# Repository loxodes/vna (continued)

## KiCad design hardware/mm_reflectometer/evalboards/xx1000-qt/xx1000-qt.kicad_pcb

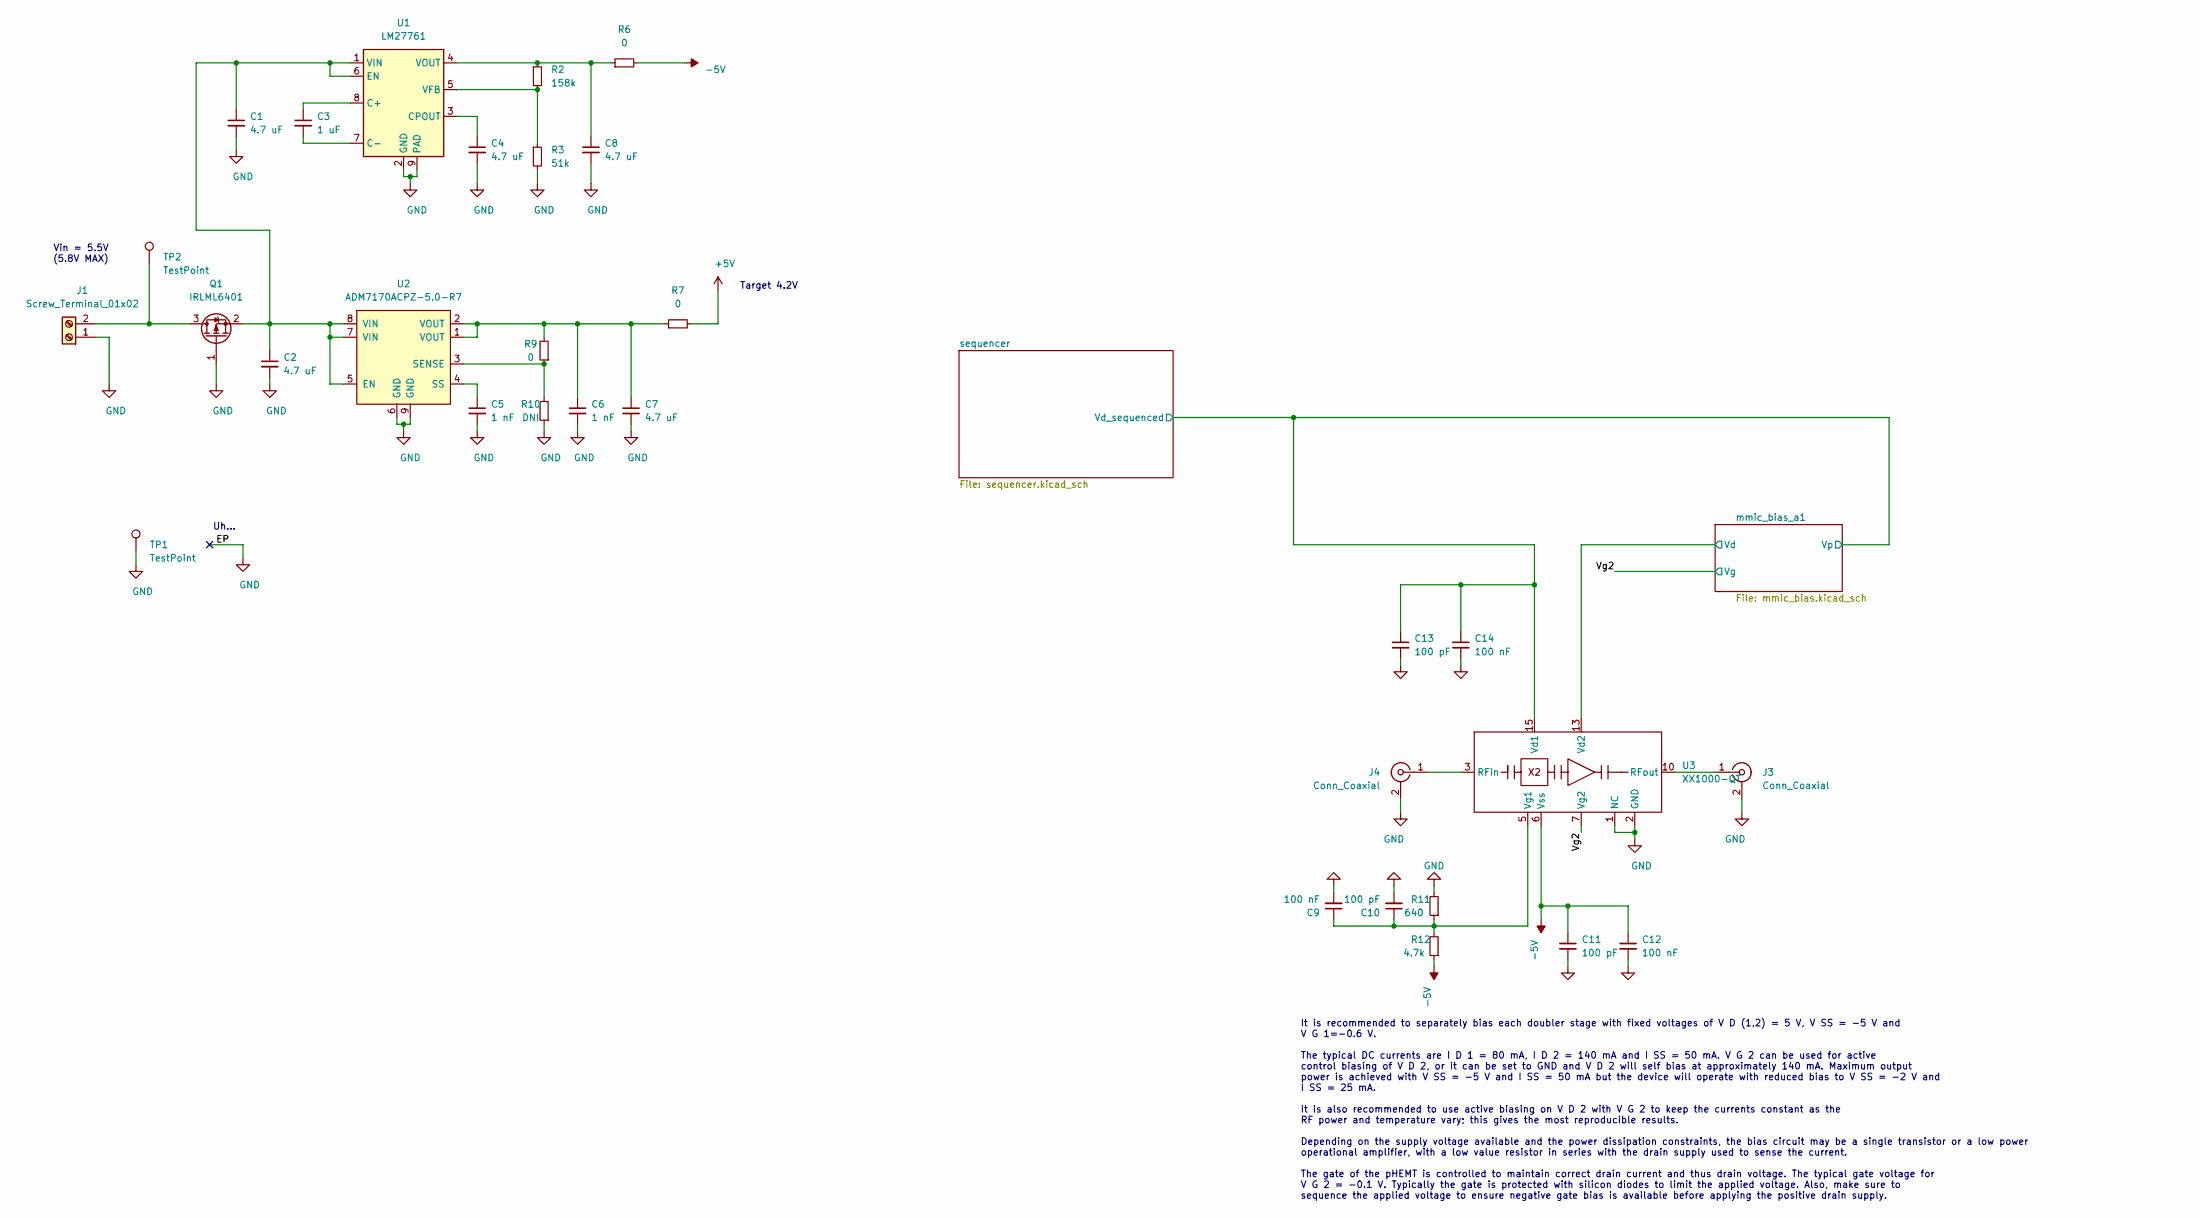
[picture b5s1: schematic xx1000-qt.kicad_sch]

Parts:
C1, C2, C4, C7, C8: 4.7 uF; C_0603_1608Metric
C3: 1 uF; C_0402_1005Metric
C5, C6: 1 nF; C_0402_1005Metric
C9, C12, C14: 100 nF; C_0402_1005Metric
C10, C11, C13: 100 pF; C_0402_1005Metric
J1: Screw_Terminal_01x02; TerminalBlock_Phoenix_MPT-0,5-2-2.54_1x02_P2.54mm_Horizontal
J3, J4: Conn_Coaxial; sw_edge_oshpark_4layer
Q1: IRLML6401; SOT-23
R2: 158k; R_0402_1005Metric
R3: 51k; R_0402_1005Metric
R6, R7, R9: 0; R_0402_1005Metric
R10: DNI; R_0402_1005Metric
R11: 640; R_0402_1005Metric
R12: 4.7k; R_0402_1005Metric
TP1, TP2: TestPoint; TestPoint_Keystone_5015_Micro-Minature
U1: LM27761; WSON-8-1EP_2x2mm_P0.5mm_EP0.9x1.6mm
U2: ADM7170ACPZ-5.0-R7; DFN-8-1EP_3x3mm_P0.5mm_EP1.66x2.38mm
U3: XX1000-QT; QFN-16-1EP_3x3mm_P0.5mm_EP1.45x1.45mm; mpn XX1000-QT-0G0T

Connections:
+5V: R7.2; also elsewhere on the board
-5V: C11.1, C12.1, R6.2, R12.1, U3.6 (Vss); also elsewhere on the board
/Vg2: U3.7 (Vg2); also elsewhere on the board
/mmic_bias_a1/Vd: U3.13 (Vd2); also elsewhere on the board
/mmic_bias_a1/Vp: C13.1, C14.1, U3.15 (Vd1); also elsewhere on the board
GND: C1.2, C2.2, C4.2, C5.2, C6.2, C7.2, C8.2, C9.2, C10.2, C11.2, C12.2, C13.2, C14.2, J1.1, J3.2 (Ext), J4.2 (Ext), Q1.1 (G), R3.2, R10.1, R11.2, TP1.1, U1.2 (GND), U1.9 (PAD), U2.6 (GND), U2.9 (GND), U3.1 (NC), U3.2 (GND), U3.4 (GND), U3.8 (NC), U3.9 (GND), U3.11 (GND), U3.12 (NC), U3.14 (NC), U3.16 (NC), U3.17 (GND); also elsewhere on the board
unnamed: C1.1, C2.1, Q1.2 (S), U1.1 (VIN), U1.6 (EN), U2.5 (EN), U2.7 (VIN), U2.8 (VIN)
unnamed: C3.1, U1.8 (C+)
unnamed: C3.2, U1.7 (C-)
unnamed: C4.1, U1.3 (CPOUT)
unnamed: C5.1, U2.4 (SS)
unnamed: C6.1, C7.1, R7.1, R9.2, U2.1 (VOUT), U2.2 (VOUT)
unnamed: C8.1, R2.1, R6.1, U1.4 (VOUT)
unnamed: C9.1, C10.1, R11.1, R12.2, U3.5 (Vg1)
unnamed: J1.2, Q1.3 (D), TP2.1
unnamed: J3.1 (In), U3.10 (RFout)
unnamed: J4.1 (In), U3.3 (RFin)
unnamed: R2.2, R3.1, U1.5 (VFB)
unnamed: R9.1, R10.2, U2.3 (SENSE)

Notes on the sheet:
Vin = 5.5V (5.8V MAX)
Uh...
Target 4.2V
It is recommended to separately bias each doubler stage with fixed voltages of V D (1,2) = 5 V, V SS = -5 V and V G 1=-0.6 V. The typical DC currents are I D 1 = 80 mA, I D 2 = 140 mA and I SS = 50 mA. V G 2 can be used for active control biasing of V D 2, or it can be set to GND and V D 2 will sel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

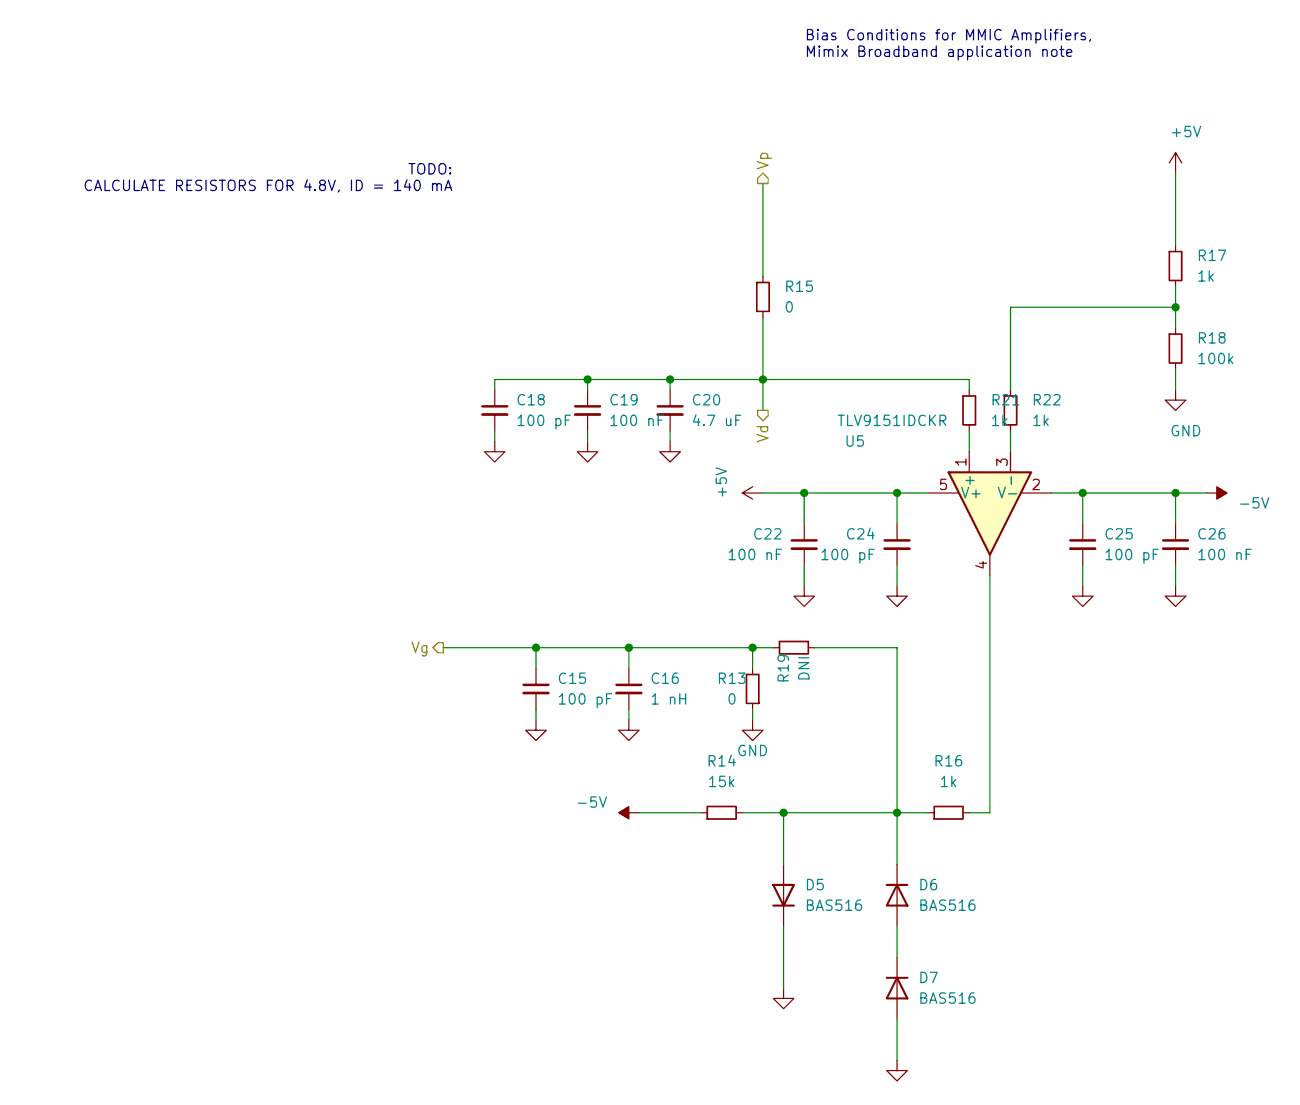
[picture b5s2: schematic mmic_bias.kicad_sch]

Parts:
C15, C18, C24, C25: 100 pF; C_0402_1005Metric
C16: 1 nH; C_0402_1005Metric
C19, C22, C26: 100 nF; C_0402_1005Metric
C20: 4.7 uF; C_0603_1608Metric
D5, D6, D7: BAS516; D_SOD-523
R13: 0; R_0402_1005Metric
R14: 15k; R_0402_1005Metric
R15: 0; R_0603_1608Metric
R16, R17, R21, R22: 1k; R_0402_1005Metric
R18: 100k; R_0402_1005Metric
R19: DNI; R_0402_1005Metric
U5: TLV9151IDCKR; SOT-353_SC-70-5

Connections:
+5V: C22.1, C24.1, R17.1, U5.5 (V+); also elsewhere on the board
-5V: C25.1, C26.1, R14.1, U5.2 (V-); also elsewhere on the board
/Vg2: C15.1, C16.1, R13.2, R19.2; also elsewhere on the board
/mmic_bias_a1/Vd: C18.1, C19.1, C20.1, R15.2, R21.1; also elsewhere on the board
/mmic_bias_a1/Vp: R15.1; also elsewhere on the board
GND: C15.2, C16.2, C18.2, C19.2, C20.2, C22.2, C24.2, C25.2, C26.2, D5.1 (K), D7.2 (A), R13.1, R18.2; also elsewhere on the board
unnamed: D5.2 (A), D6.1 (K), R14.2, R16.1, R19.1
unnamed: D6.2 (A), D7.1 (K)
unnamed: R16.2, U5.4
unnamed: R17.2, R18.1, R22.1
unnamed: R21.2, U5.1 (+)
unnamed: R22.2, U5.3 (-)

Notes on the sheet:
TODO: CALCULATE RESISTORS FOR 4.8V, ID = 140 mA
Bias Conditions for MMIC Amplifiers, Mimix Broadband application note

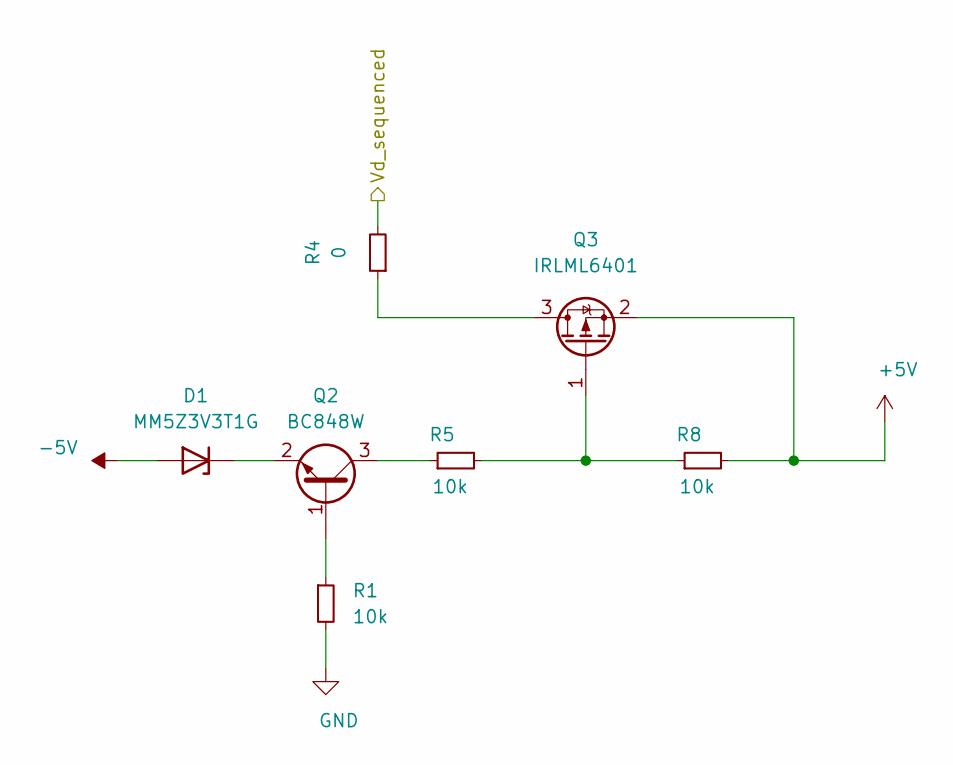
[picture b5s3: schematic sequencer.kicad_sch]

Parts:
D1: MM5Z3V3T1G; D_SOD-523
Q2: BC848W; SOT-323_SC-70
Q3: IRLML6401; SOT-23
R1, R5, R8: 10k; R_0402_1005Metric
R4: 0; R_0402_1005Metric

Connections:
+5V: Q3.2 (S), R8.2; also elsewhere on the board
-5V: D1.2 (A); also elsewhere on the board
/mmic_bias_a1/Vp: R4.2; also elsewhere on the board
GND: R1.2; also elsewhere on the board
unnamed: D1.1 (K), Q2.2 (E)
unnamed: Q2.1 (B), R1.1
unnamed: Q2.3 (C), R5.1
unnamed: Q3.1 (G), R5.2, R8.1
unnamed: Q3.3 (D), R4.1

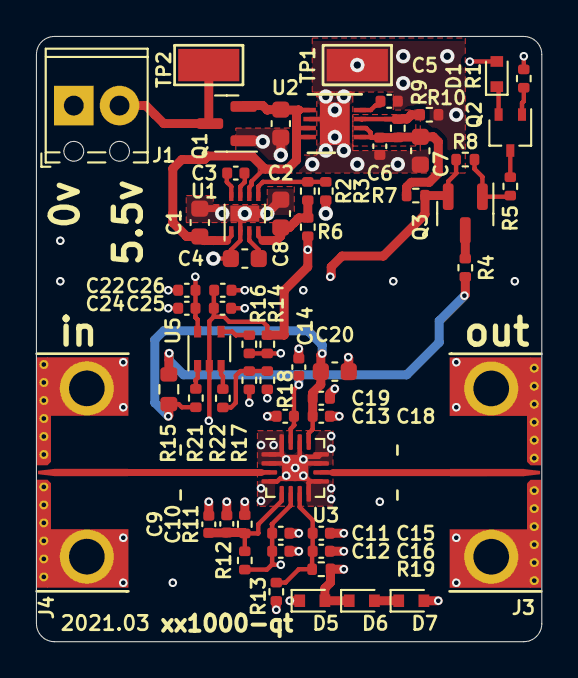
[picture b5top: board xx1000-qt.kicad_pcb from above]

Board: 4 copper layers, 28.1 x 33.6 mm, 60 parts (0 on the bottom side), 30 nets.

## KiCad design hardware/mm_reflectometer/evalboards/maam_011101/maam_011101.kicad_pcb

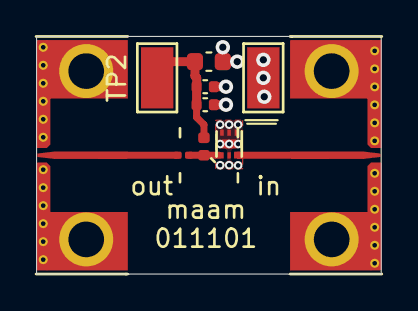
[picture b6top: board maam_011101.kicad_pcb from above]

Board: 4 copper layers, 19.2 x 13.2 mm, 10 parts (0 on the bottom side), 4 nets.

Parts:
C1: 100 pF; C_0402_1005Metric
C2: 100 pF; C_0201_0603Metric
C3: 100 nF; C_0402_1005Metric
C4: 10 uF; C_0603_1608Metric
J1, J2: Conn_Coaxial; sw_edge_oshpark_4layer
L1: BLM15GG471; L_0402_1005Metric
TP1, TP2: TestPoint; TestPoint_Keystone_5015_Micro-Minature
U1: MAAM-011101; TDFN6

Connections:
GND: C1.2, C3.2, C4.2, J1.2 (Ext), J2.2 (Ext), TP1.1, U1.2 (NC), U1.4 (NC), U1.5 (NC), U1.6 (NC), U1.7 (EP)
unnamed: C1.1, C3.1, C4.1, L1.1, TP2.1
unnamed: C2.1, L1.2, U1.1 (RFout)
unnamed: J2.1 (In), U1.3 (RFin)

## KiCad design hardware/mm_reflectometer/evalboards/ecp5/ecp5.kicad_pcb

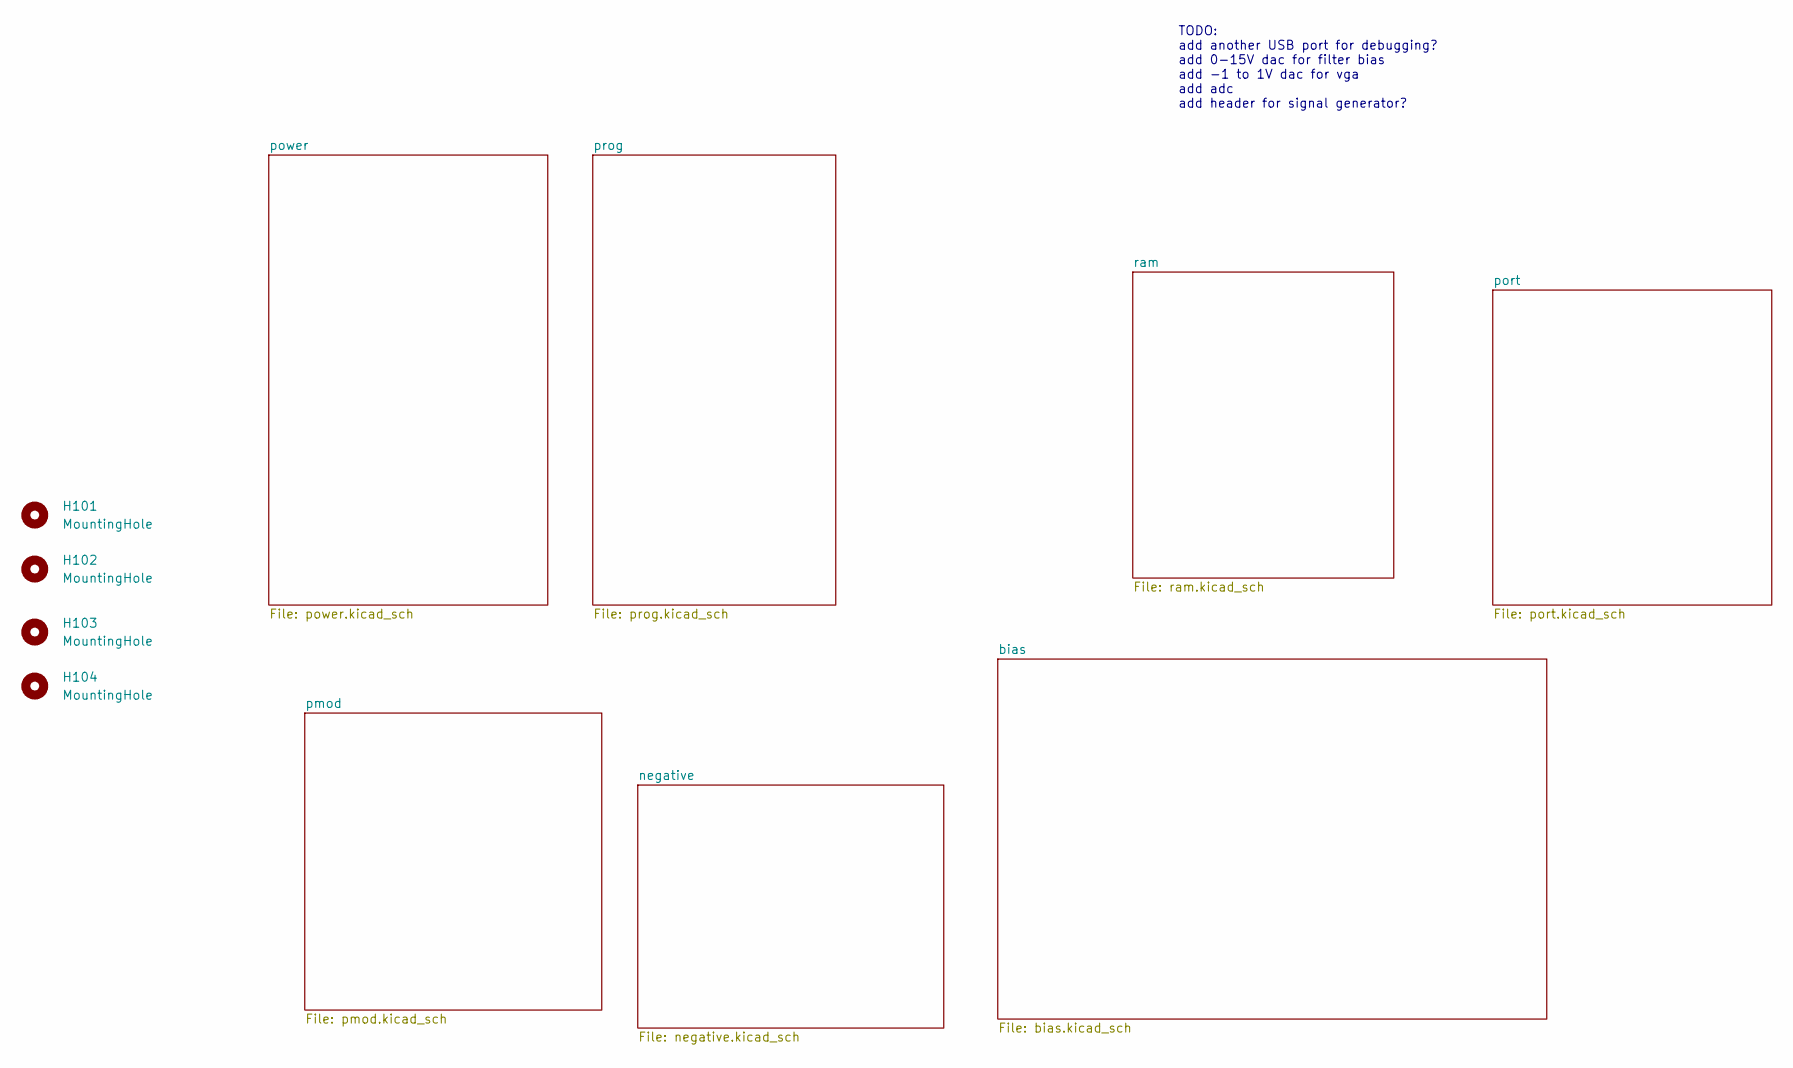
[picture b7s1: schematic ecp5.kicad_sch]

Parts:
H101, H102, H103, H104: MountingHole; MountingHole_2.7mm_M2.5

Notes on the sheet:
TODO: add another USB port for debugging? add 0-15V dac for filter bias add -1 to 1V dac for vga add adc add header for signal generator?

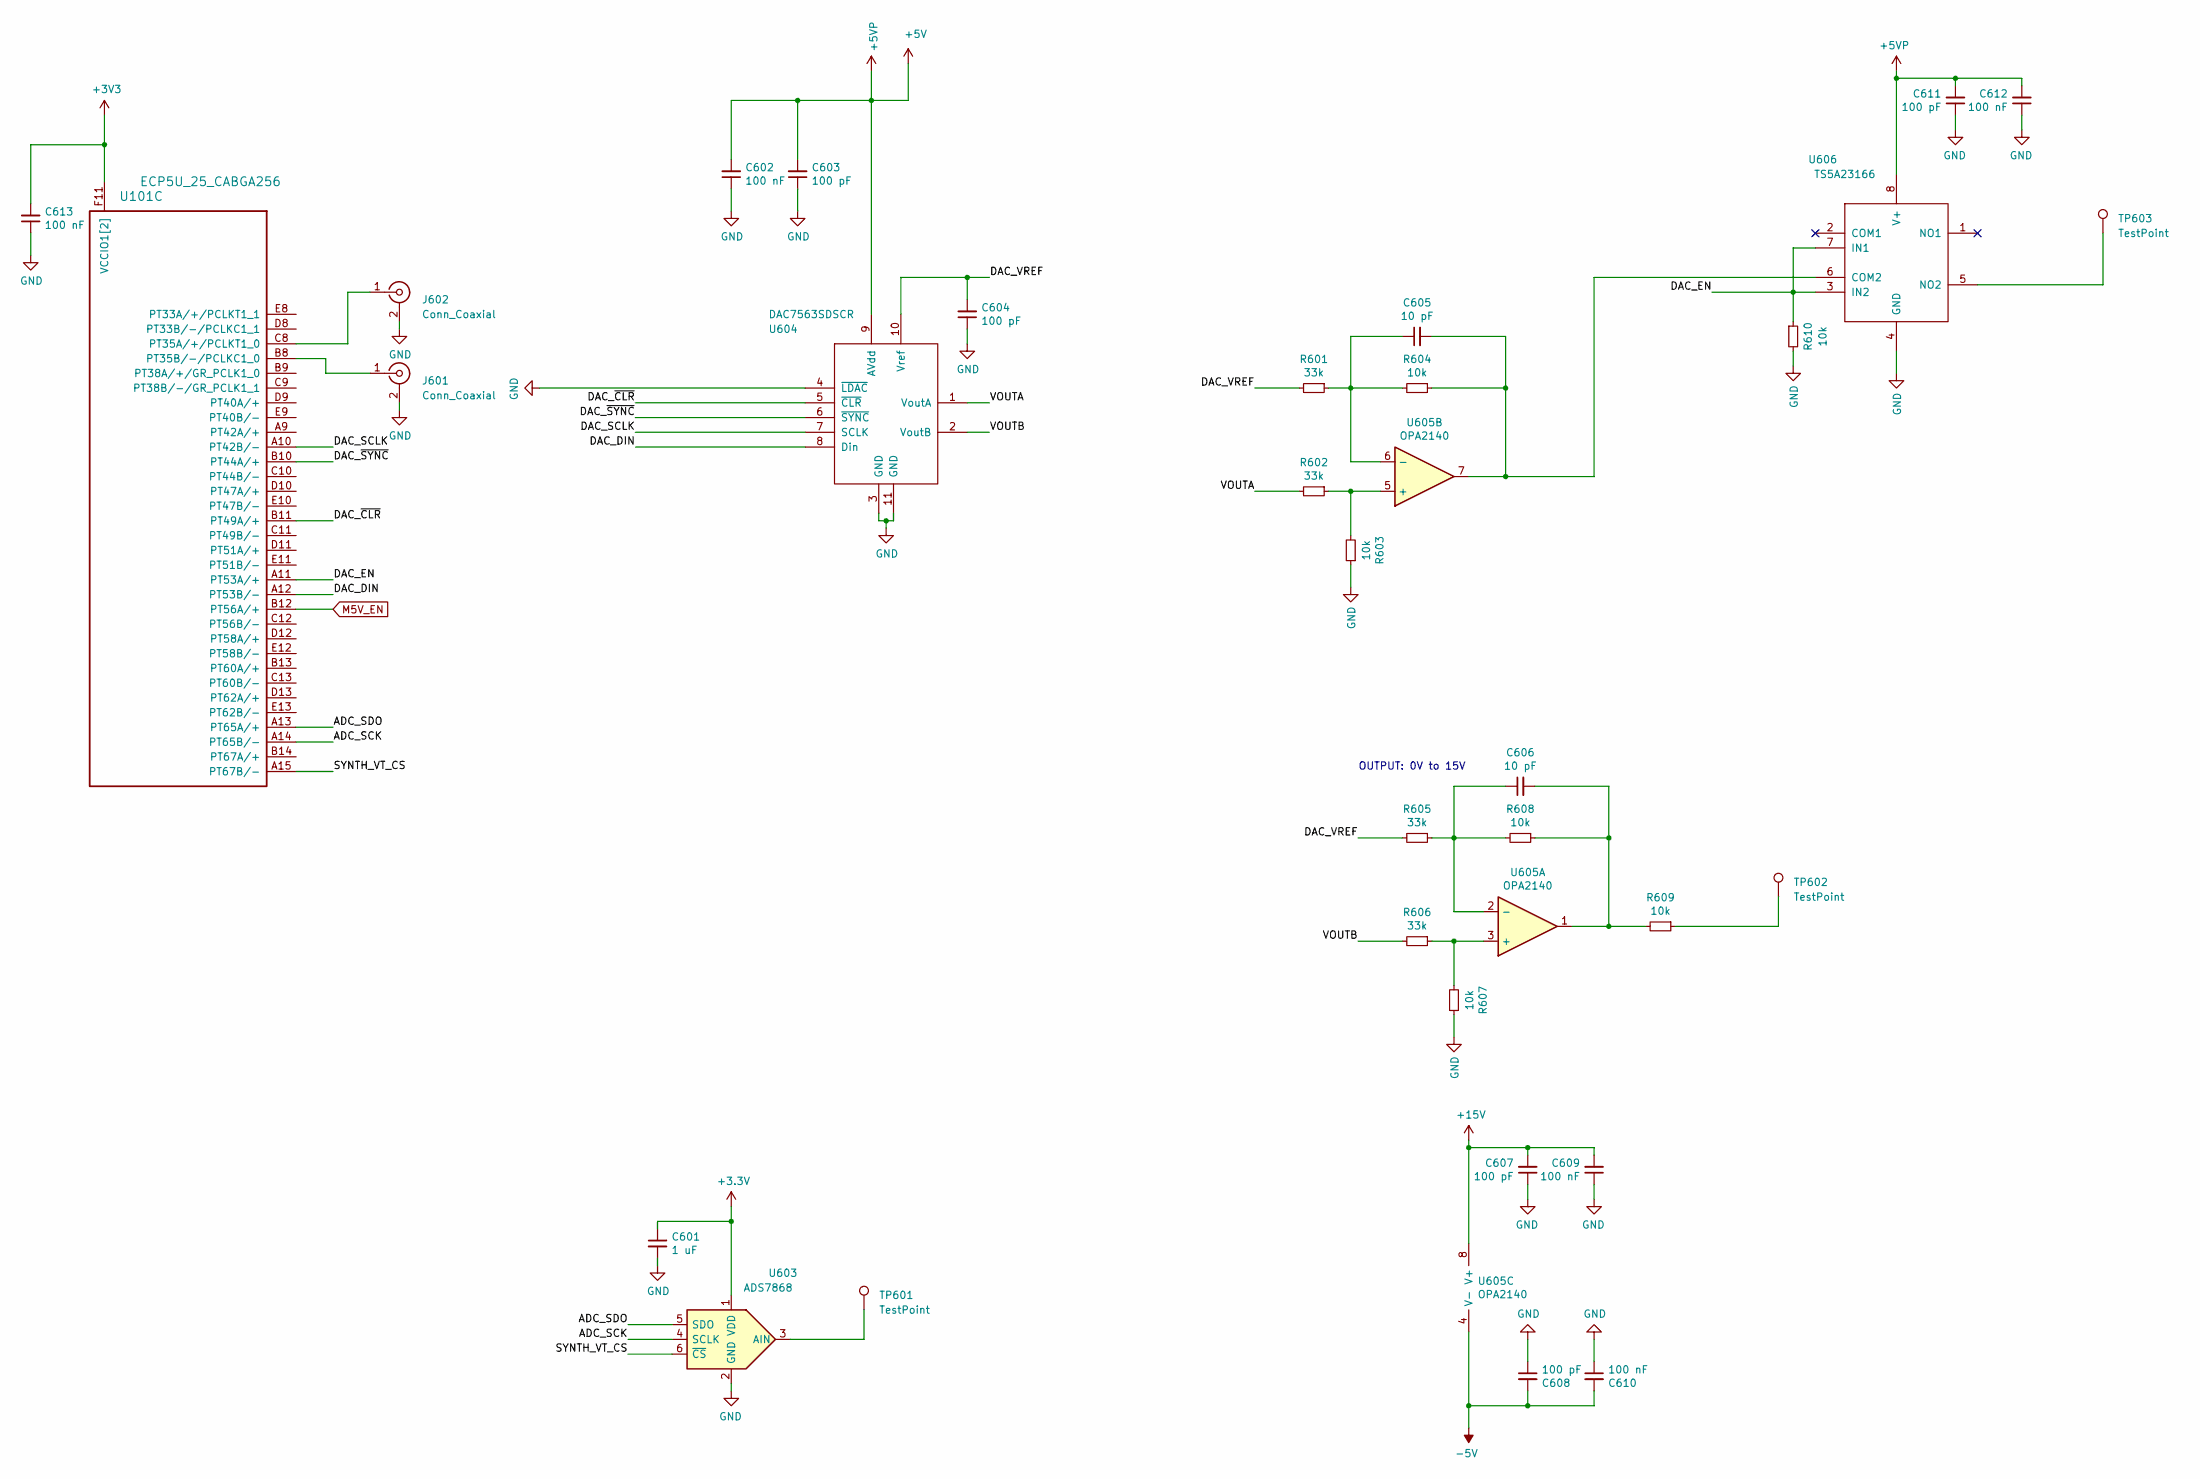
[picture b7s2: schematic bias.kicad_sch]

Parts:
C601: 1 uF; C_0402_1005Metric
C602, C609, C610, C612, C613: 100 nF; C_0402_1005Metric
C603, C604, C607, C608, C611: 100 pF; C_0402_1005Metric
C605, C606: 10 pF; C_0402_1005Metric
J601, J602: Conn_Coaxial; U.FL_Molex_MCRF_73412-0110_Vertical
R601, R602, R605, R606: 33k; R_0402_1005Metric
R603, R604, R607, R608, R609, R610: 10k; R_0402_1005Metric
TP601, TP602, TP603: TestPoint; TestPoint_Keystone_5015_Micro-Minature
U101: ECP5U_25_CABGA256; BGA-256_14.0x14.0mm_Layout16x16_P0.8mm_Ball0.45mm_Pad0.32mm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
U603: ADS7868; TSOT-23-6
U604: DAC7563SDSCR; DFN-10_PWSON_N10_3x3mm_P0.5mm_EP1.05x2.55mm
U605: OPA2140; MSOP-8_3x3mm_P0.65mm
U606: TS5A23166; VSSOP-8

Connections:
+5V: C602.2, C603.2, C611.2, C612.2, U604.9 (AVdd), U606.8 (V+); also elsewhere on the board
+15V: C607.2, C609.2, U605.8 (V+); also elsewhere on the board
-5V: C608.2, C610.2, U605.4 (V-); also elsewhere on the board
/bias/ADC_SCK: U101.A14 (PT65B/-), U603.4 (SCLK)
/bias/ADC_SDO: U101.A13 (PT65A/+), U603.5 (SDO)
/bias/DAC_DIN: U101.A12 (PT53B/-), U604.8 (Din)
/bias/DAC_EN: R610.1, U101.A11 (PT53A/+), U606.3 (IN2), U606.7 (IN1)
/bias/DAC_SCLK: U101.A10 (PT42B/-), U604.7 (SCLK)
/bias/DAC_VREF: C604.2, R601.2, R605.2, U604.10 (Vref)
/bias/DAC_~CLR: U101.B11 (PT49A/+), U604.5 (~CLR)
/bias/DAC_~SYNC: U101.B10 (PT44A/+), U604.6 (~SYNC)
/bias/SYNTH_VT_CS: U101.A15 (PT67B/-), U603.6 (~CS)
/bias/VOUTA: R602.2, U604.1 (VoutA)
/bias/VOUTB: R606.2, U604.2 (VoutB)
GND: C601.2, C602.1, C603.1, C604.1, C607.1, C608.1, C609.1, C610.1, C611.1, C612.1, C613.1, J601.2 (Ext), J602.2 (Ext), R603.1, R607.1, R610.2, U603.2 (GND), U604.3 (GND), U604.4 (~LDAC), U604.11 (GND), U606.4 (GND); also elsewhere on the board
M5V_EN: U101.B12 (PT56A/+); also elsewhere on the board
unnamed: C605.1, R601.1, R604.2, U605.6 (-)
unnamed: C605.2, R604.1, U605.7, U606.6 (COM2)
unnamed: C606.1, R605.1, R608.2, U605.2 (-)
unnamed: C606.2, R608.1, R609.2, U605.1
unnamed: J601.1 (In), U101.B8 (PT35B/-/PCLKC1_0)
unnamed: J602.1 (In), U101.C8 (PT35A/+/PCLKT1_0)
unnamed: R602.1, R603.2, U605.5 (+)
unnamed: R606.1, R607.2, U605.3 (+)
unnamed: R609.1, TP602.1
unnamed: TP601.1, U603.3 (AIN)
unnamed: TP603.1, U606.5 (NO2)

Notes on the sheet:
OUTPUT: 0V to 15V

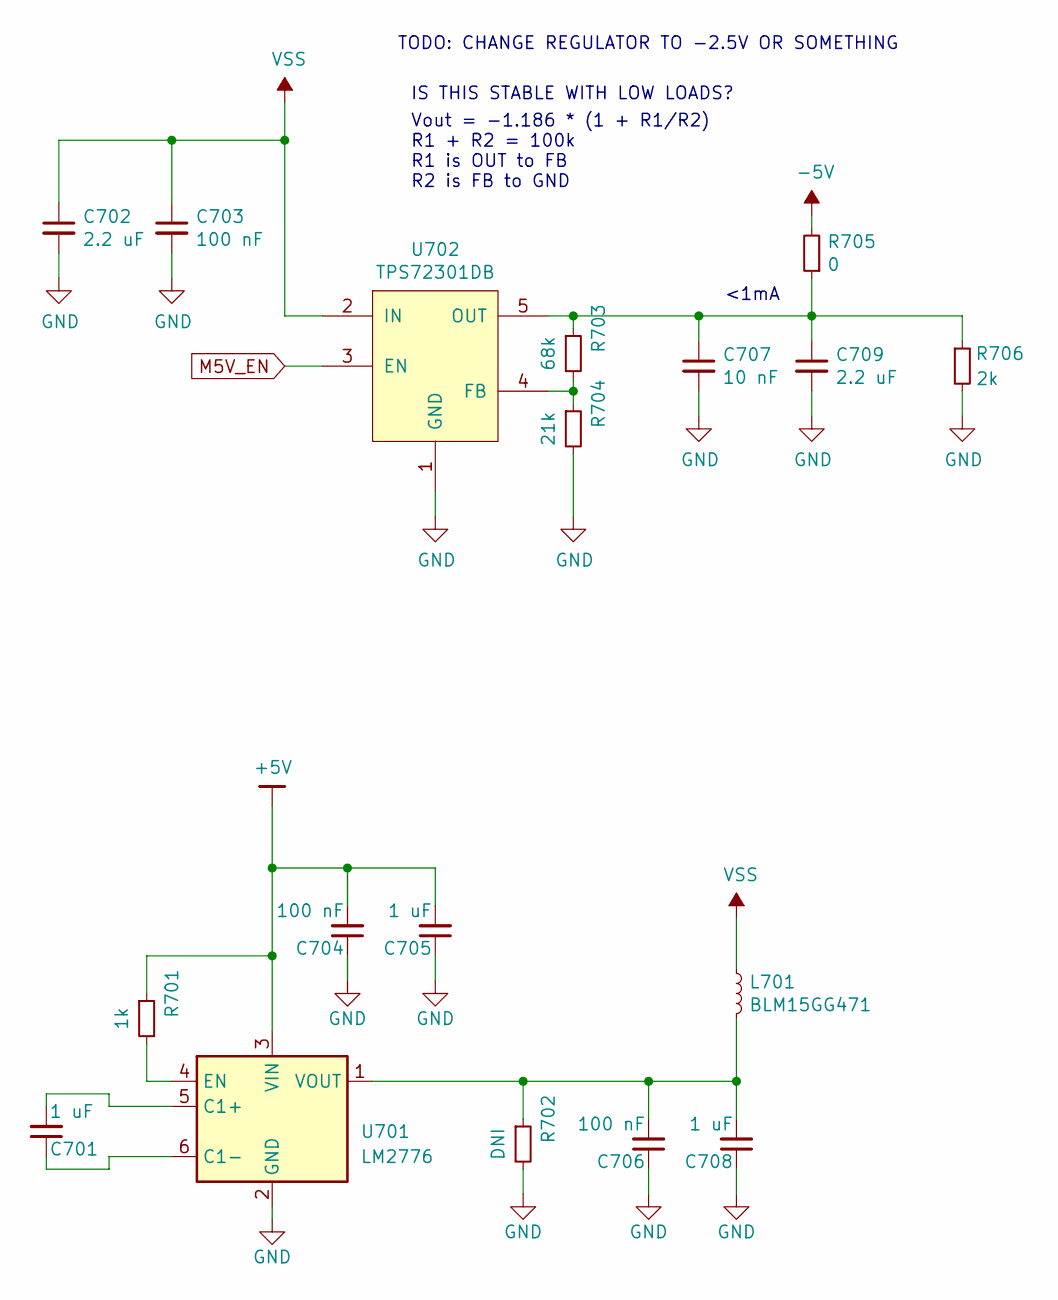
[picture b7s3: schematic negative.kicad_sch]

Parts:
C701, C705, C708: 1 uF; C_0402_1005Metric
C702, C709: 2.2 uF; C_0603_1608Metric
C703, C704, C706: 100 nF; C_0402_1005Metric
C707: 10 nF; C_0402_1005Metric
L701: BLM15GG471; L_0402_1005Metric
R701: 1k; R_0402_1005Metric
R702: DNI; R_0402_1005Metric
R703: 68k; R_0402_1005Metric
R704: 21k; R_0402_1005Metric
R705: 0; R_0603_1608Metric
R706: 2k; R_0402_1005Metric
U701: LM2776; SOT-23-6
U702: TPS72301DB; SOT-23-5

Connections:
+5V: C704.2, C705.2, R701.1, U701.3 (VIN); also elsewhere on the board
-5V: R705.2; also elsewhere on the board
GND: C702.2, C703.2, C704.1, C705.1, C706.1, C707.2, C708.1, C709.2, R702.2, R704.2, R706.2, U701.2 (GND), U702.1 (GND); also elsewhere on the board
M5V_EN: U702.3 (EN); also elsewhere on the board
unnamed: C701.1, U701.6 (C1-)
unnamed: C701.2, U701.5 (C1+)
unnamed: C706.2, C708.2, L701.2, R702.1, U701.1 (VOUT)
unnamed: C707.1, C709.1, R703.1, R705.1, R706.1, U702.5 (OUT)
unnamed: R701.2, U701.4 (EN)
unnamed: R703.2, R704.1, U702.4 (FB)
VSS: C702.1, C703.1, L701.1, U702.2 (IN)

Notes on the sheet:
IS THIS STABLE WITH LOW LOADS?
Vout = -1.186 * (1 + R1/R2) R1 + R2 = 100k R1 is OUT to FB R2 is FB to GND
<1mA
TODO: CHANGE REGULATOR TO -2.5V OR SOMETHING

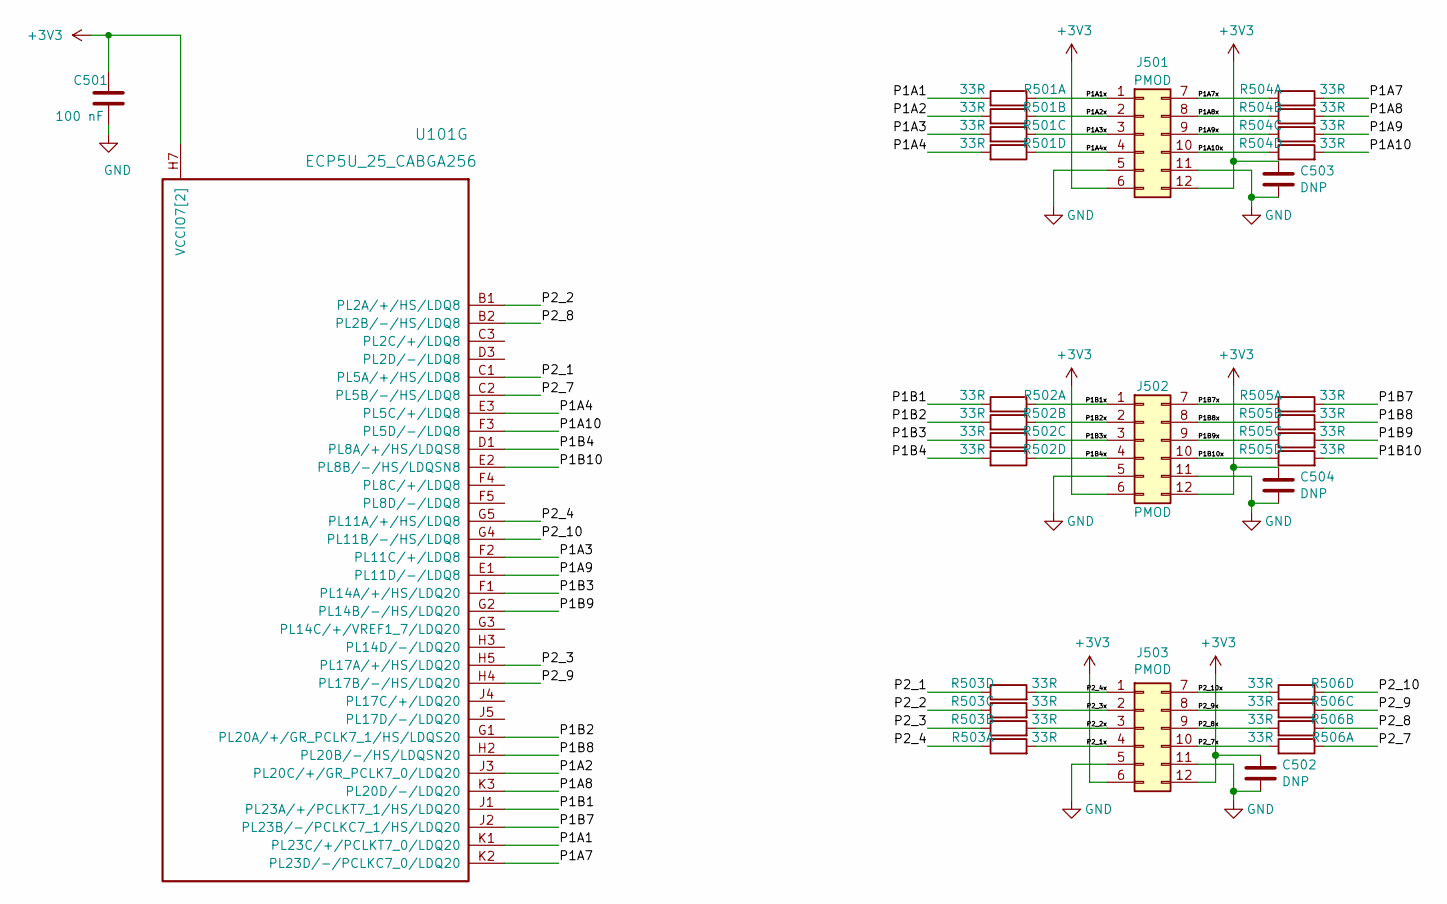
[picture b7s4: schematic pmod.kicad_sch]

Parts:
C501: 100 nF; C_0402_1005Metric
C502, C503, C504: DNP; C_0603_1608Metric
J501, J502, J503: PMOD; PMOD_Angled_2x06
R501, R502, R503, R504, R505, R506: 33R; R_Array_Convex_4x0402
U101: ECP5U_25_CABGA256; BGA-256_14.0x14.0mm_Layout16x16_P0.8mm_Ball0.45mm_Pad0.32mm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

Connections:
/pmod/P1A1: R501.1, U101.K1 (PL23C/+/PCLKT7_0/LDQ20)
/pmod/P1A1x: J501.1, R501.8
/pmod/P1A2: R501.2, U101.J3 (PL20C/+/GR_PCLK7_0/LDQ20)
/pmod/P1A2x: J501.2, R501.7
/pmod/P1A3: R501.3, U101.F2 (PL11C/+/LDQ8)
/pmod/P1A3x: J501.3, R501.6
/pmod/P1A4: R501.4, U101.E3 (PL5C/+/LDQ8)
/pmod/P1A4x: J501.4, R501.5
/pmod/P1A7: R504.1, U101.K2 (PL23D/-/PCLKC7_0/LDQ20)
/pmod/P1A7x: J501.7, R504.8
/pmod/P1A8: R504.2, U101.K3 (PL20D/-/LDQ20)
/pmod/P1A8x: J501.8, R504.7
/pmod/P1A9: R504.3, U101.E1 (PL11D/-/LDQ8)
/pmod/P1A9x: J501.9, R504.6
/pmod/P1A10: R504.4, U101.F3 (PL5D/-/LDQ8)
/pmod/P1A10x: J501.10, R504.5
/pmod/P1B1: R502.1, U101.J1 (PL23A/+/PCLKT7_1/HS/LDQ20)
/pmod/P1B1x: J502.1, R502.8
/pmod/P1B2: R502.2, U101.G1 (PL20A/+/GR_PCLK7_1/HS/LDQS20)
/pmod/P1B2x: J502.2, R502.7
/pmod/P1B3: R502.3, U101.F1 (PL14A/+/HS/LDQ20)
/pmod/P1B3x: J502.3, R502.6
/pmod/P1B4: R502.4, U101.D1 (PL8A/+/HS/LDQS8)
/pmod/P1B4x: J502.4, R502.5
/pmod/P1B7: R505.1, U101.J2 (PL23B/-/PCLKC7_1/HS/LDQ20)
/pmod/P1B7x: J502.7, R505.8
/pmod/P1B8: R505.2, U101.H2 (PL20B/-/HS/LDQSN20)
/pmod/P1B8x: J502.8, R505.7
/pmod/P1B9: R505.3, U101.G2 (PL14B/-/HS/LDQ20)
/pmod/P1B9x: J502.9, R505.6
/pmod/P1B10: R505.4, U101.E2 (PL8B/-/HS/LDQSN8)
/pmod/P1B10x: J502.10, R505.5
/pmod/P2_1: R503.5, U101.C1 (PL5A/+/HS/LDQ8)
/pmod/P2_1x: J503.4, R503.1
/pmod/P2_2: R503.6, U101.B1 (PL2A/+/HS/LDQ8)
/pmod/P2_2x: J503.3, R503.2
/pmod/P2_3: R503.7, U101.H5 (PL17A/+/HS/LDQ20)
/pmod/P2_3x: J503.2, R503.3
/pmod/P2_4: R503.8, U101.G5 (PL11A/+/HS/LDQ8)
/pmod/P2_4x: J503.1, R503.4
/pmod/P2_7: R506.8, U101.C2 (PL5B/-/HS/LDQ8)
/pmod/P2_7x: J503.10, R506.1
/pmod/P2_8: R506.7, U101.B2 (PL2B/-/HS/LDQ8)
/pmod/P2_8x: J503.9, R506.2
/pmod/P2_9: R506.6, U101.H4 (PL17B/-/HS/LDQ20)
/pmod/P2_9x: J503.8, R506.3
/pmod/P2_10: R506.5, U101.G4 (PL11B/-/HS/LDQ8)
/pmod/P2_10x: J503.7, R506.4
GND: C501.2, C502.1, C503.1, C504.1, J501.5, J501.11, J502.5, J502.11, J503.5, J503.11; also elsewhere on the board

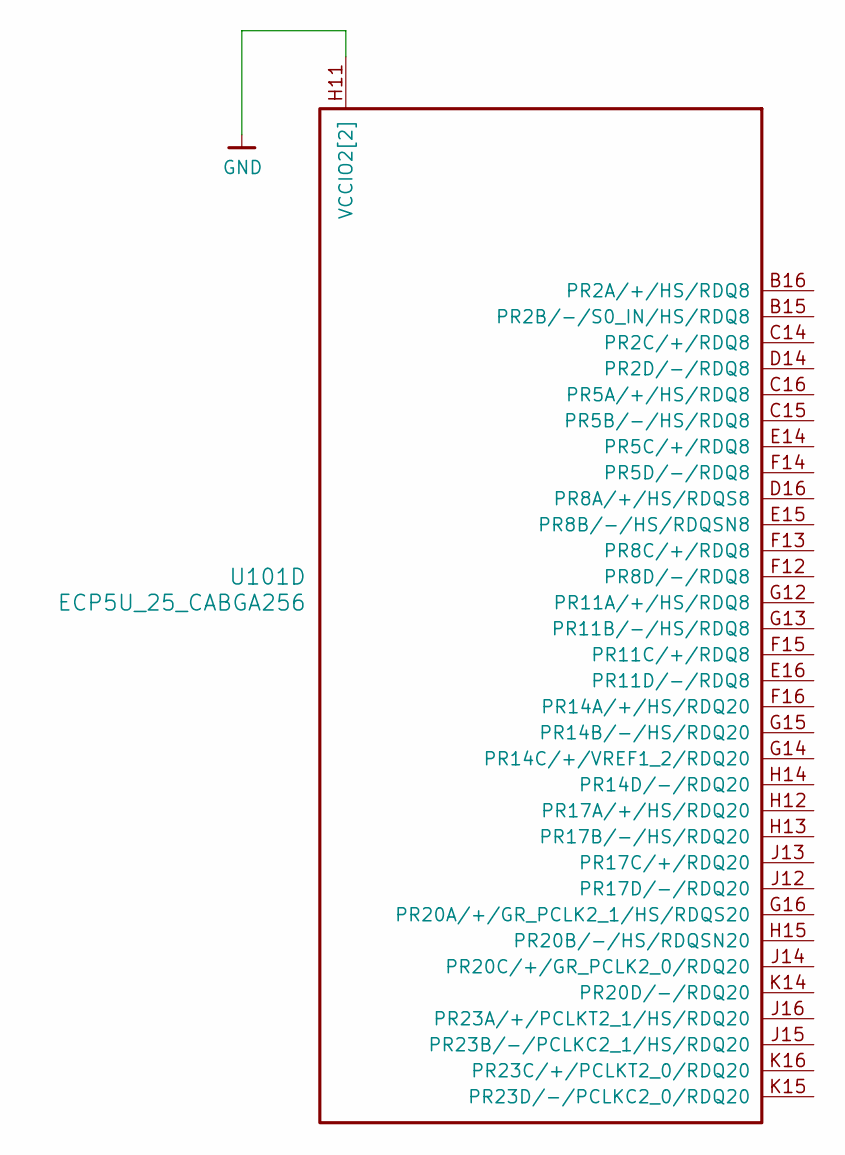
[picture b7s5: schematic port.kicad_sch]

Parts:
U101: ECP5U_25_CABGA256; BGA-256_14.0x14.0mm_Layout16x16_P0.8mm_Ball0.45mm_Pad0.32mm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

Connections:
GND: U101.H11 (VCCIO2[2]), U101.J11 (VCCIO2[2]); also elsewhere on the board
